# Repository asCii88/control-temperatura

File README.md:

# control-temperatura
Room temperature control through web interface. RF network of sensor/actuators

* Board --> Contine los archivos necesarios para realizar los PCB

* Codigo Fuente Varios --> Contiene el codigo para arduino del Esclavo y el Master y el programa serial

* Proyecto --> Pagina Web

Para Wamp: C:\wamp\www
Para XAMPP: C:\xampp\htdocs

* sistema --> Base de datos

Para Wamp: C:\wamp\bin\mysql\mysql5.6.17\data
Para XAMPP: C:\xampp\mysql\data .

Librerias necesarias:
DHT-sensor-library-master
RF24-master
mysql-connector-net-6.9.8

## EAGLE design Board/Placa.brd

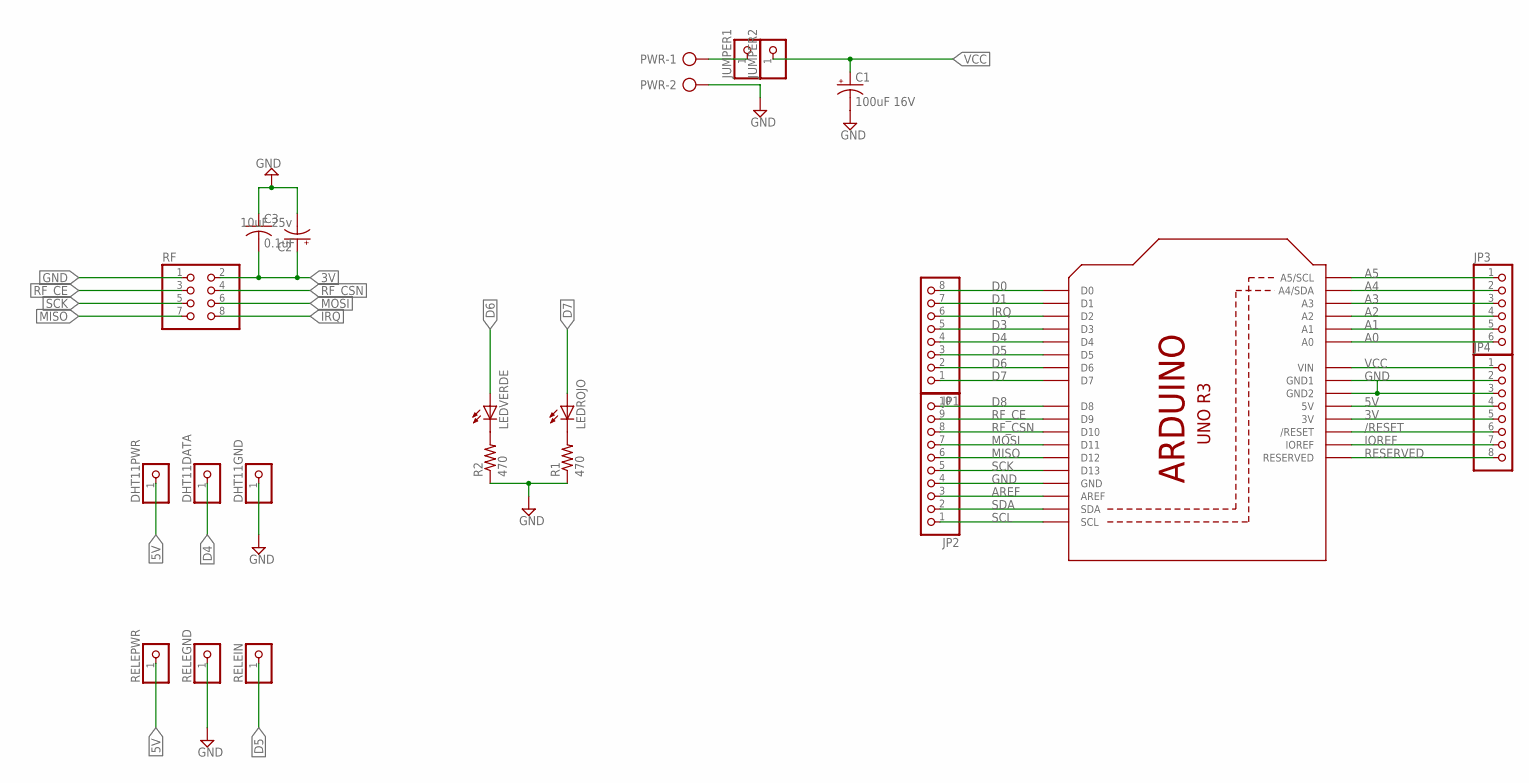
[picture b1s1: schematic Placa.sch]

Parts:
C1: 100uF 16V; E2,5-7
C2: 10uF 25v; E2,5-7
C3: 0.1uF; C050-024X044
DHT11DATA, DHT11GND, DHT11PWR: PINHD-1X1; 1X01
JP1, JP4: PINHD-1X8; 1X08
JP2: PINHD-1X10; 1X10
JP3: PINHD-1X6; 1X06
JUMPER1, JUMPER2: PINHD-1X1; 1X01
LEDROJO: LED5MM
LEDVERDE: LED5MM
PWR: AK500/2-H
R1, R2: 470; 0204/7
RELEGND: PINHD-1X1; 1X01
RELEIN: PINHD-1X1; 1X01
RELEPWR: PINHD-1X1; 1X01
RF: PINHD-2X4; 2X04
U1: ARDUINOR3-DIMENSION; ARDUINOR3

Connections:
3V: C2.+, C3.2, JP4.5, RF.2, U1.3V
5V: DHT11PWR.1, JP4.4, RELEPWR.1, U1.5V
/RESET: JP4.6, U1.RESET (/RESET)
A0: JP3.6, U1.A0
A1: JP3.5, U1.A1
A2: JP3.4, U1.A2
A3: JP3.3, U1.A3
A4: JP3.2, U1.A4 (A4/SDA)
A5: JP3.1, U1.A5 (A5/SCL)
AREF: JP2.3, U1.AREF
D0: JP1.8, U1.D0
D1: JP1.7, U1.D1
D3: JP1.5, U1.D3
D4: DHT11DATA.1, JP1.4, U1.D4
D5: JP1.3, RELEIN.1, U1.D5
D6: JP1.2, LEDVERDE.A, U1.D6
D7: JP1.1, LEDROJO.A, U1.D7
D8: JP2.10, U1.D8
GND: C1.-, C2.-, C3.1, DHT11GND.1, JP2.4, JP4.2, JP4.3, PWR.2, R1.1, R2.1, RELEGND.1, RF.1, U1.GND, U1.GND1, U1.GND2
IOREF: JP4.7, U1.IOREF
IRQ: JP1.6, RF.8, U1.D2
MISO: JP2.6, RF.7, U1.D12
MOSI: JP2.7, RF.6, U1.D11
unnamed: LEDVERDE.K (C), R2.2
unnamed: LEDROJO.K (C), R1.2
unnamed: JUMPER1.1, PWR.1
RESERVED: JP4.8, U1.RESERVED
RF_CE: JP2.9, RF.3, U1.D9
RF_CSN: JP2.8, RF.4, U1.D10
SCK: JP2.5, RF.5, U1.D13
SCL: JP2.1, U1.SCL
SDA: JP2.2, U1.SDA
VCC: C1.+, JP4.1, JUMPER2.1, U1.VIN

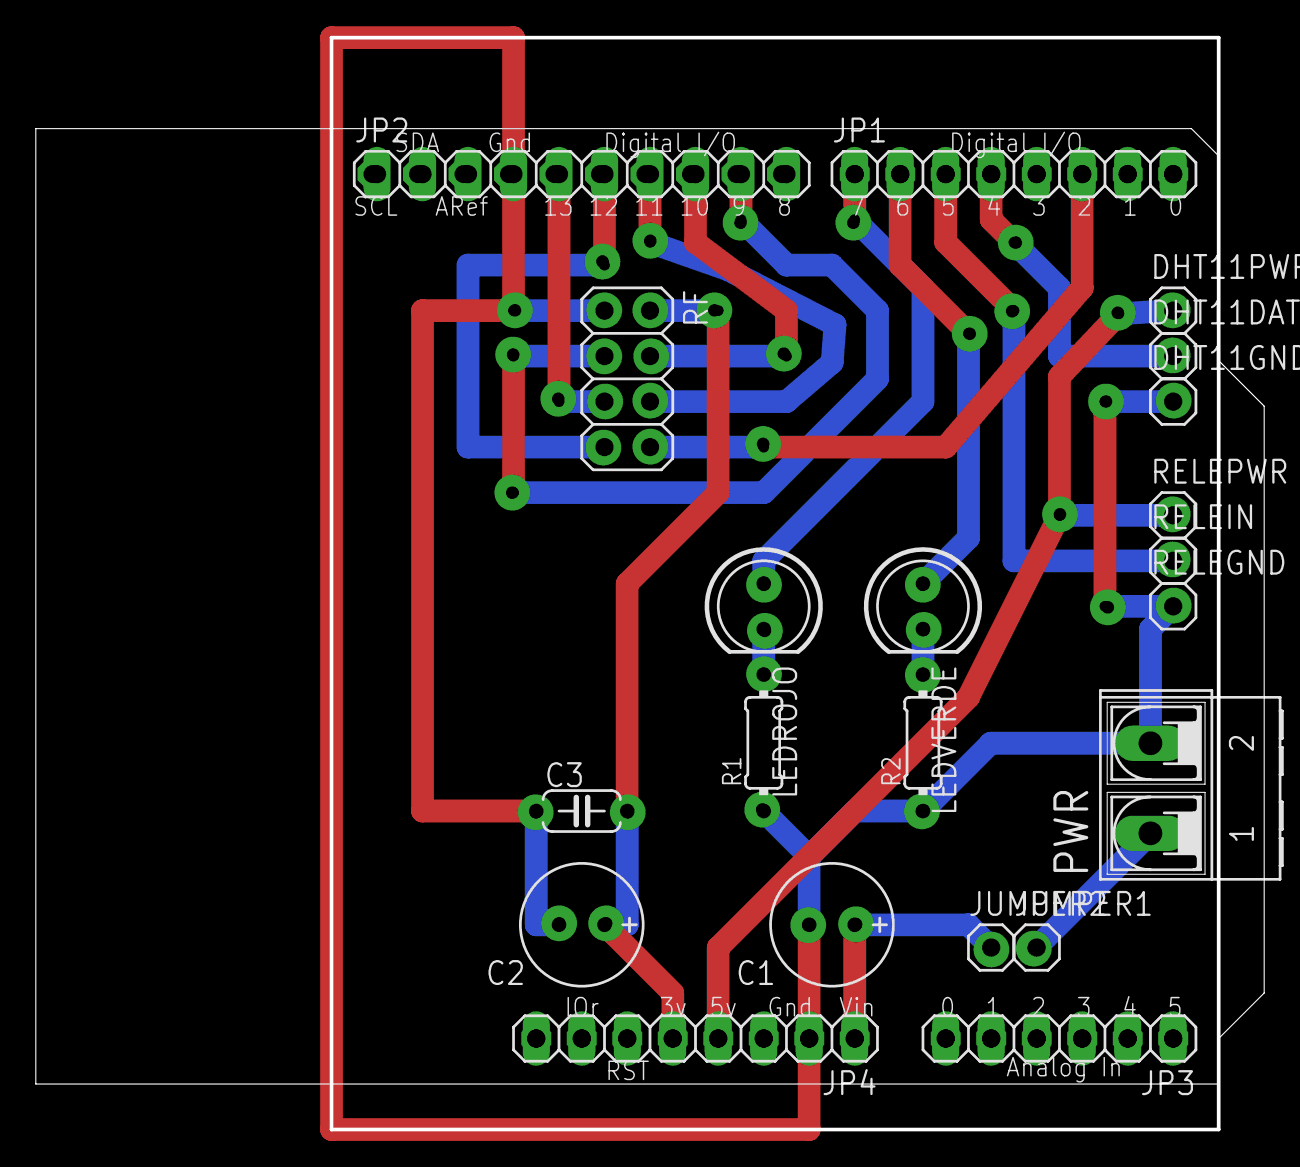
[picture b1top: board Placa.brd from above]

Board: 2 copper layers, 68.4 x 61.0 mm, 22 parts (0 on the bottom side), 33 nets.

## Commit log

2016-03-14 Added files via upload
